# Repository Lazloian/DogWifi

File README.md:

# DogWifi

Project for tracking the movement of my dog using an esp32 and accelerometer. Data sent to raspberry pi connected to wifi, read through node-red, and displayed using graphana. A custom pcb was made for the the electrical components and a case was designed and 3D printed to attach to the collar.

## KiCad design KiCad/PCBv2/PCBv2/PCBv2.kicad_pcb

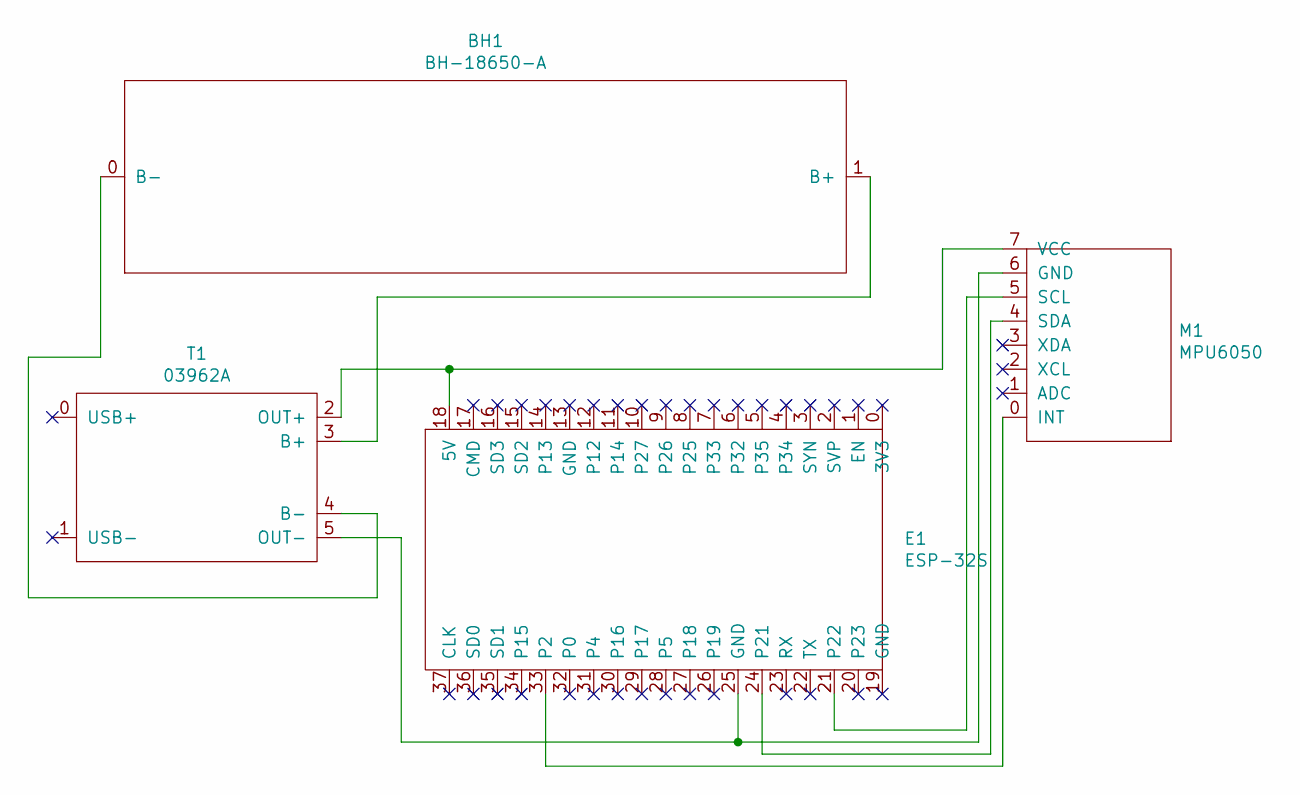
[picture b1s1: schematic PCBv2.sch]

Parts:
BH1: BH-18650-A
E1: ESP-32S
M1: MPU6050
T1: 03962A

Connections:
unnamed: BH1.0 (B-), T1.4 (B-)
unnamed: BH1.1 (B+), T1.3 (B+)
unnamed: E1.18 (5V), M1.7 (VCC~), T1.2 (OUT+)
unnamed: E1.21 (P22), M1.5 (SCL~)
unnamed: E1.24 (P21), M1.4 (SDA~)
unnamed: E1.25 (GND), M1.6 (GND~), T1.5 (OUT-)
unnamed: E1.33 (P2), M1.0 (INT)

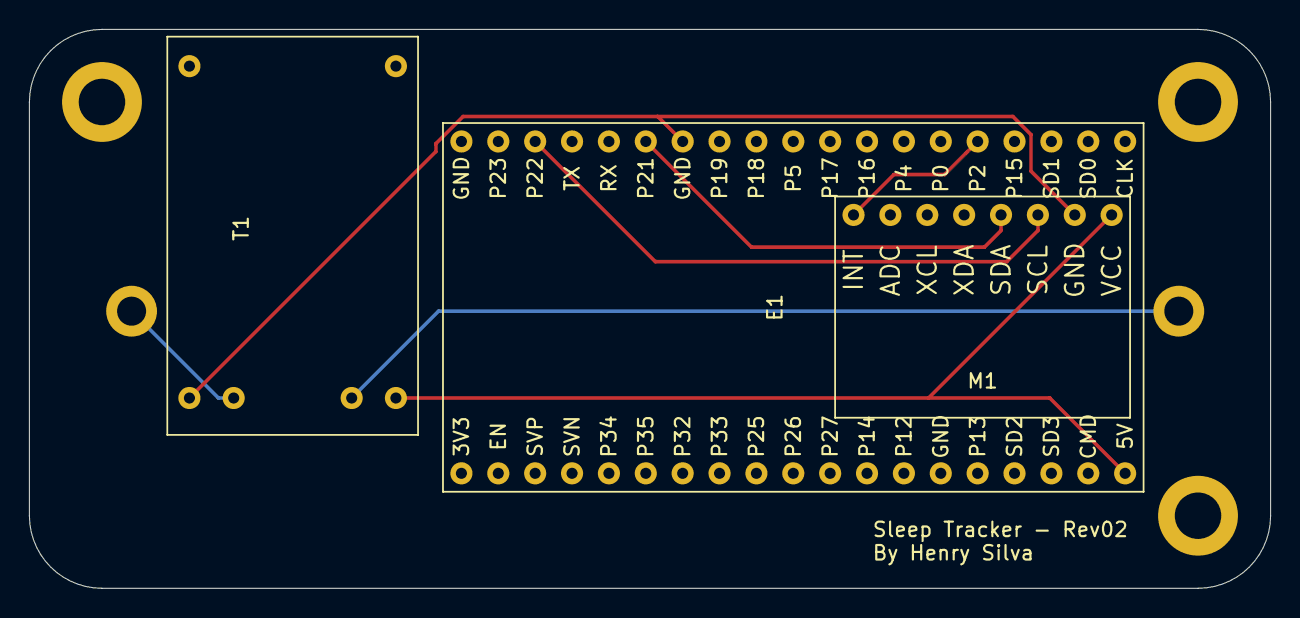
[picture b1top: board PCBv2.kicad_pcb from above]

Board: 2 copper layers, 85.5 x 38.5 mm, 4 parts (1 on the bottom side), 7 nets.
